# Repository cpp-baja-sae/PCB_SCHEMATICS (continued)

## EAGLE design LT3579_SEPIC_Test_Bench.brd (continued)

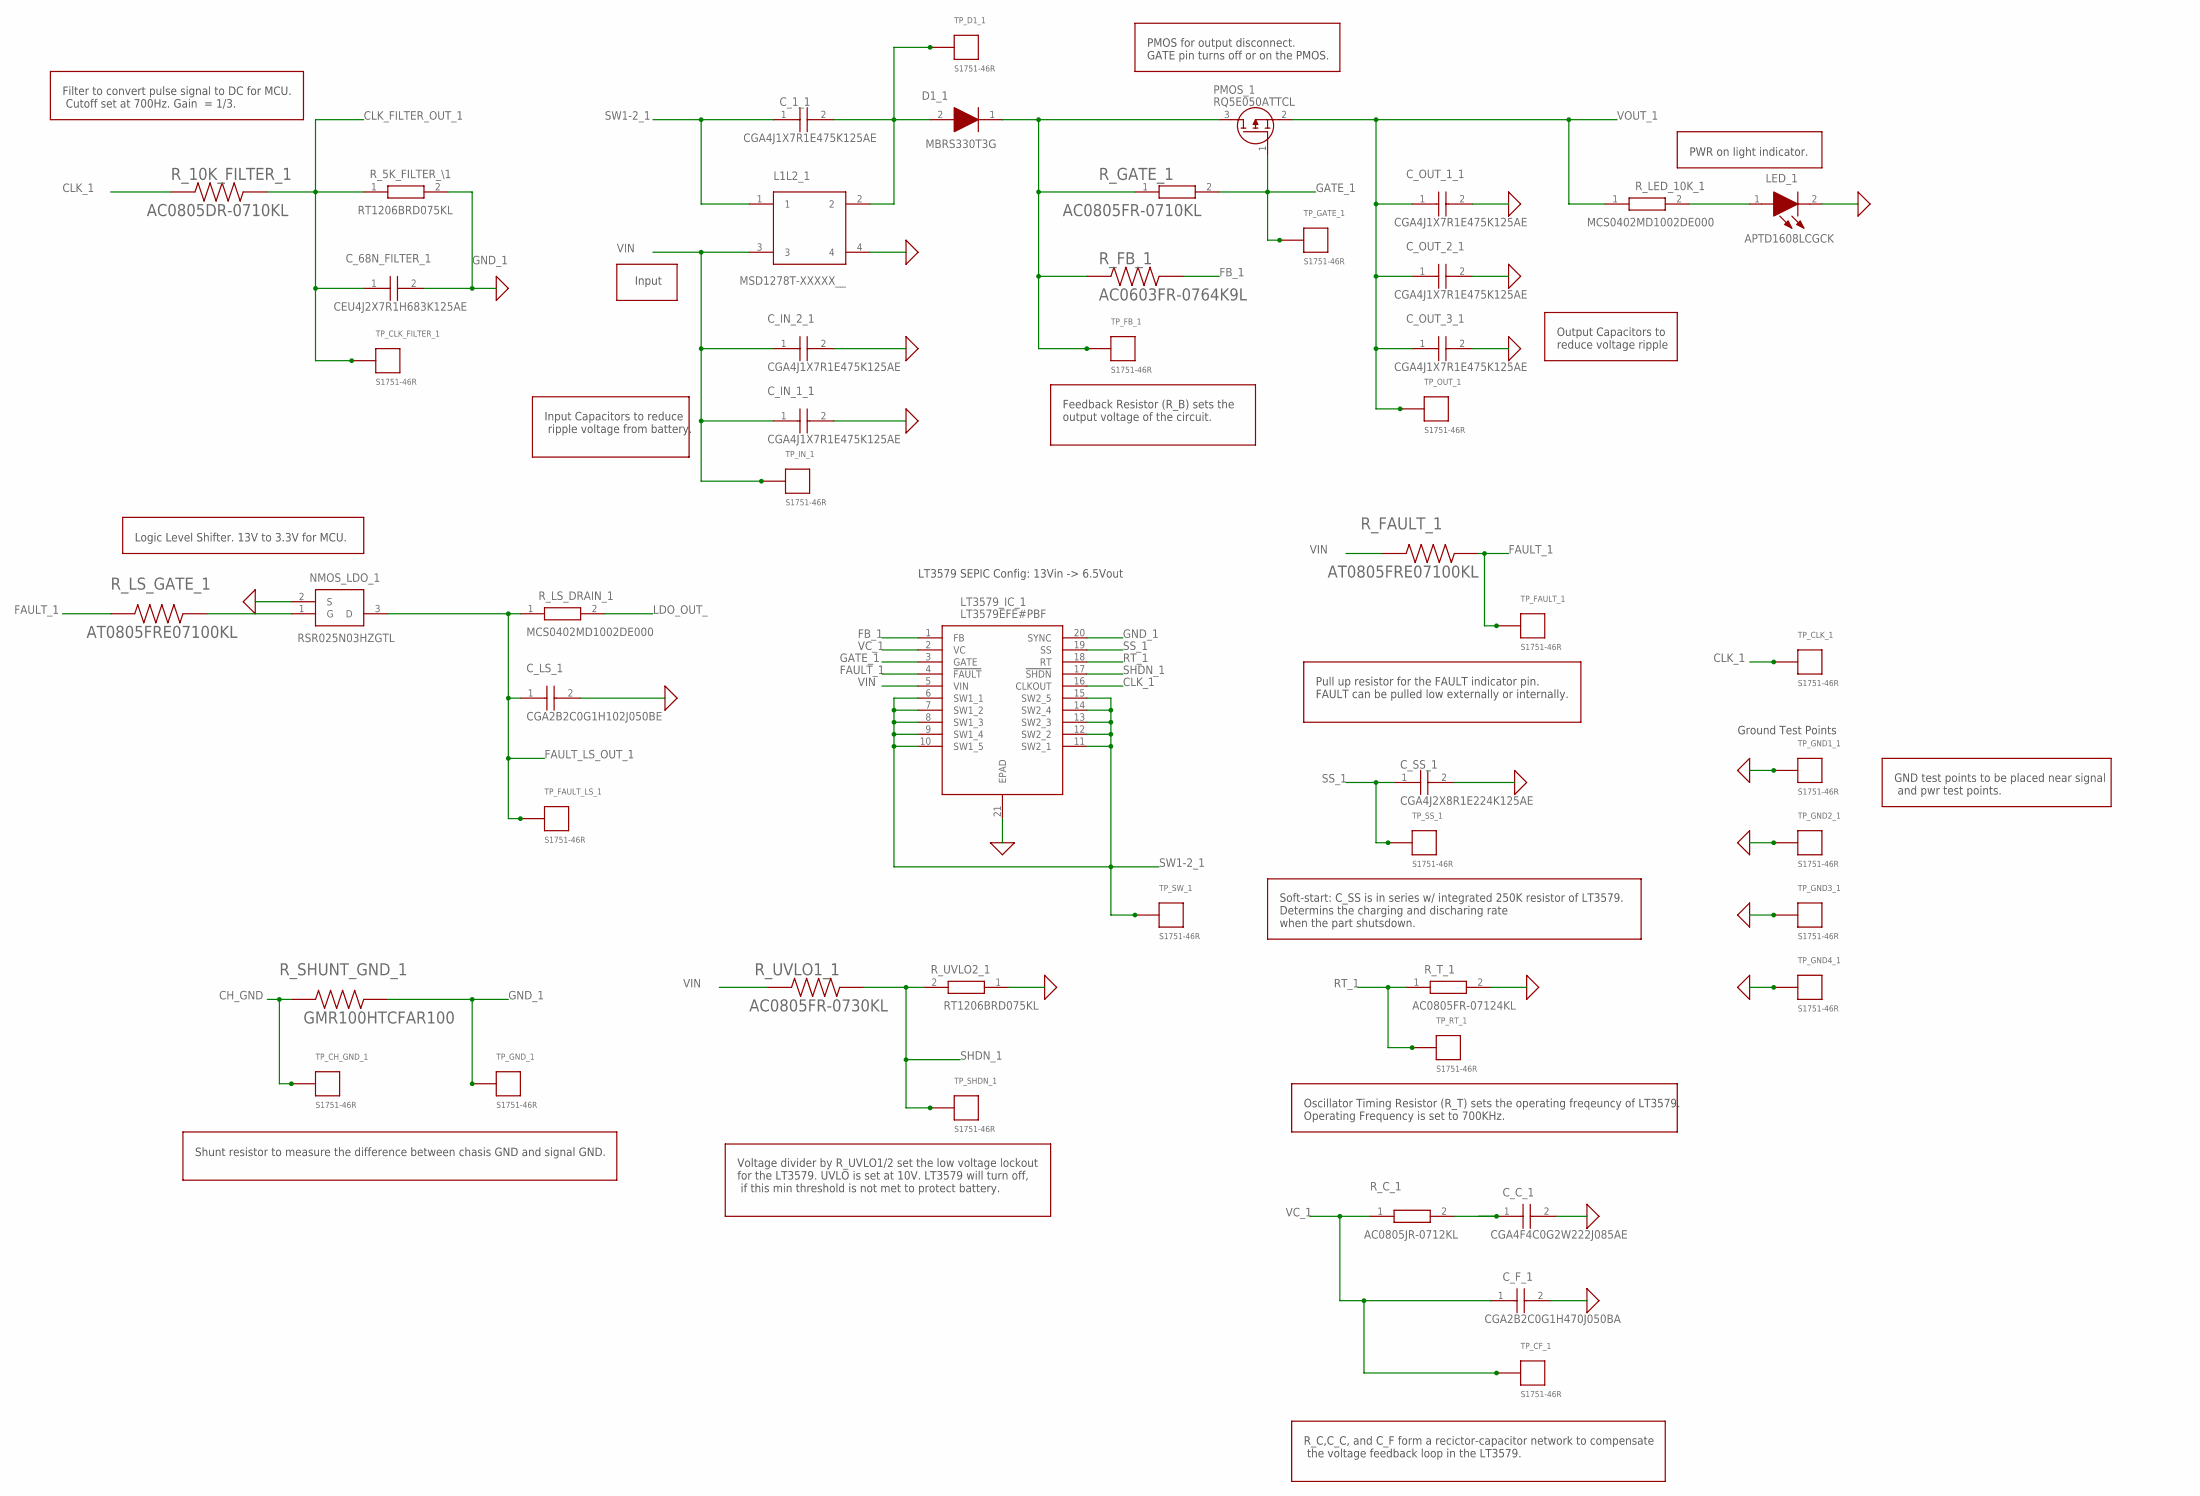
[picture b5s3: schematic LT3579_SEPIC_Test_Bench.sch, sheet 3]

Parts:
C_1_1: CGA4J1X7R1E475K125AE; CAPC2012X145N
C_68N_FILTER_1: CEU4J2X7R1H683K125AE; CAPC2013X150N
C_C_1: CGA4F4C0G2W222J085AE; CAPC2012X100N
C_F_1: CGA2B2C0G1H470J050BA; CAPC1005X55N
C_IN_1_1, C_IN_2_1: CGA4J1X7R1E475K125AE; CAPC2012X145N
C_LS_1: CGA2B2C0G1H102J050BE; CAPC1005X55N
C_OUT_1_1, C_OUT_2_1, C_OUT_3_1: CGA4J1X7R1E475K125AE; CAPC2012X145N
C_SS_1: CGA4J2X8R1E224K125AE; CAPC2012X145N
D1_1: MBRS330T3G; DIOM7958X256N
L1L2_1: MSD1278T-XXXXX__; MSD1278T-822MLXX
LED_1: APTD1608LCGCK; APT1608CGCK
LT3579_IC_1: LT3579EFE#PBF; SOP65P640X120-21N
NMOS_LDO_1: RSR025N03HZGTL; SOT95P280X100-3N
PMOS_1: RQ5E050ATTCL; SOT95P280X100-3N
R_5K_FILTER_\1: RT1206BRD075KL; RESC3116X65N
R_10K_FILTER_1: AC0805DR-0710KL; RESC2012X60N
R_C_1: AC0805JR-0712KL; RESC2012X60N
R_FAULT_1: AT0805FRE07100KL; RESC2012X60N
R_FB_1: AC0603FR-0764K9L; RESC1608X55N
R_GATE_1: AC0805FR-0710KL; RESC2012X60N
R_LED_10K_1: MCS0402MD1002DE000; RESC1005X37N
R_LS_DRAIN_1: MCS0402MD1002DE000; RESC1005X37N
R_LS_GATE_1: AT0805FRE07100KL; RESC2012X60N
R_SHUNT_GND_1: GMR100HTCFAR100; RESC6432X55N
R_T_1: AC0805FR-07124KL; RESC2012X60N
R_UVLO1_1: AC0805FR-0730KL; RESC2012X60N
R_UVLO2_1: RT1206BRD075KL; RESC3116X65N
TP_CF_1: S1751-46R; S1751-46R_
TP_CH_GND_1: S1751-46R; S1751-46R_
TP_CLK_1: S1751-46R; S1751-46R_
TP_CLK_FILTER_1: S1751-46R; S1751-46R_
TP_D1_1: S1751-46R; S1751-46R_
TP_FAULT_1: S1751-46R; S1751-46R_
TP_FAULT_LS_1: S1751-46R; S1751-46R_
TP_FB_1: S1751-46R; S1751-46R_
TP_GATE_1: S1751-46R; S1751-46R_
TP_GND1_1, TP_GND2_1, TP_GND3_1, TP_GND4_1: S1751-46R; S1751-46R_
TP_GND_1: S1751-46R; S1751-46R_
TP_IN_1: S1751-46R; S1751-46R_
TP_OUT_1: S1751-46R; S1751-46R_
TP_RT_1: S1751-46R; S1751-46R_
TP_SHDN_1: S1751-46R; S1751-46R_
TP_SS_1: S1751-46R; S1751-46R_
TP_SW_1: S1751-46R; S1751-46R_

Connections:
CH_GND: R_SHUNT_GND_1.1, TP_CH_GND_1.1; also elsewhere on the board
CLK_1: LT3579_IC_1.16 (CLKOUT), R_10K_FILTER_1.1, TP_CLK_1.1; also elsewhere on the board
FAULT_1: LT3579_IC_1.4 (!FAULT), R_FAULT_1.1, R_LS_GATE_1.1, TP_FAULT_1.1
FAULT_LS_OUT_1: C_LS_1.1, NMOS_LDO_1.3 (D), R_LS_DRAIN_1.1, TP_FAULT_LS_1.1; also elsewhere on the board
FB_1: LT3579_IC_1.1 (FB), R_FB_1.2
GATE_1: LT3579_IC_1.3 (GATE), PMOS_1.1 (G), R_GATE_1.2, TP_GATE_1.1
GND_1: C_68N_FILTER_1.2, C_C_1.2, C_F_1.2, C_IN_1_1.2, C_IN_2_1.2, C_LS_1.2, C_OUT_1_1.2, C_OUT_2_1.2, C_OUT_3_1.2, C_SS_1.2, L1L2_1.4, LED_1.2 (K), LT3579_IC_1.20 (SYNC), LT3579_IC_1.21 (EPAD), NMOS_LDO_1.2 (S), R_5K_FILTER_\1.2, R_SHUNT_GND_1.2, R_T_1.2, R_UVLO2_1.1, TP_GND1_1.1, TP_GND2_1.1, TP_GND3_1.1, TP_GND4_1.1, TP_GND_1.1; also elsewhere on the board
LDO_OUT_: R_LS_DRAIN_1.2; also elsewhere on the board
unnamed: C_1_1.2, D1_1.2 (A), L1L2_1.2, TP_D1_1.1
unnamed: C_C_1.1, R_C_1.2
unnamed: D1_1.1 (K), PMOS_1.3 (D), R_FB_1.1, R_GATE_1.1, TP_FB_1.1
unnamed: NMOS_LDO_1.1 (G), R_LS_GATE_1.2
unnamed: LED_1.1 (A), R_LED_10K_1.2
unnamed: C_68N_FILTER_1.1, R_5K_FILTER_\1.1, R_10K_FILTER_1.2, TP_CLK_FILTER_1.1
RT_1: LT3579_IC_1.18 (RT), R_T_1.1, TP_RT_1.1
SHDN_1: LT3579_IC_1.17 (!SHDN), R_UVLO1_1.1, R_UVLO2_1.2, TP_SHDN_1.1
SS_1: C_SS_1.1, LT3579_IC_1.19 (SS), TP_SS_1.1
SW1-2_1: C_1_1.1, L1L2_1.1, LT3579_IC_1.6 (SW1_1), LT3579_IC_1.7 (SW1_2), LT3579_IC_1.8 (SW1_3), LT3579_IC_1.9 (SW1_4), LT3579_IC_1.10 (SW1_5), LT3579_IC_1.11 (SW2_1), LT3579_IC_1.12 (SW2_2), LT3579_IC_1.13 (SW2_3), LT3579_IC_1.14 (SW2_4), LT3579_IC_1.15 (SW2_5), TP_SW_1.1
VC_1: C_F_1.1, LT3579_IC_1.2 (VC), R_C_1.1, TP_CF_1.1
VIN: C_IN_1_1.1, C_IN_2_1.1, L1L2_1.3, LT3579_IC_1.5 (VIN), R_FAULT_1.2, R_UVLO1_1.2, TP_IN_1.1; also elsewhere on the board
VOUT_1: C_OUT_1_1.1, C_OUT_2_1.1, C_OUT_3_1.1, PMOS_1.2 (S), R_LED_10K_1.1, TP_OUT_1.1; also elsewhere on the board

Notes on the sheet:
LT3579 SEPIC Config: 13Vin -> 6.5Vout
Ground Test Points
Filter to convert pulse signal to DC for MCU. Cutoff set at 700Hz. Gain = 1/3.
Logic Level Shifter. 13V to 3.3V for MCU.
Voltage divider by R_UVLO1/2 set the low voltage lockout for the LT3579. UVLO is set at 10V. LT3579 will turn off, if this min threshold is not met to protect battery.
R_C,C_C, and C_F form a recictor-capacitor network to compensate the voltage feedback loop in the LT3579.
Oscillator Timing Resistor (R_T) sets the operating freqeuncy of LT3579. Operating Frequency is set to 700KHz.
Soft-start: C_SS is in series w/ integrated 250K resistor of LT3579. Determins the charging and discharing rate when the part shutsdown.
GND test points to be placed near signal and pwr test points.
Pull up resistor for the FAULT indicator pin. FAULT can be pulled low externally or internally.
PWR on light indicator.
Output Capacitors to reduce voltage ripple
Feedback Resistor (R_B) sets the output voltage of the circuit.
PMOS for output disconnect. GATE pin turns off or on the PMOS.
Input Capacitors to reduce ripple voltage from battery.
Input
Shunt resistor to measure the difference between chasis GND and signal GND.

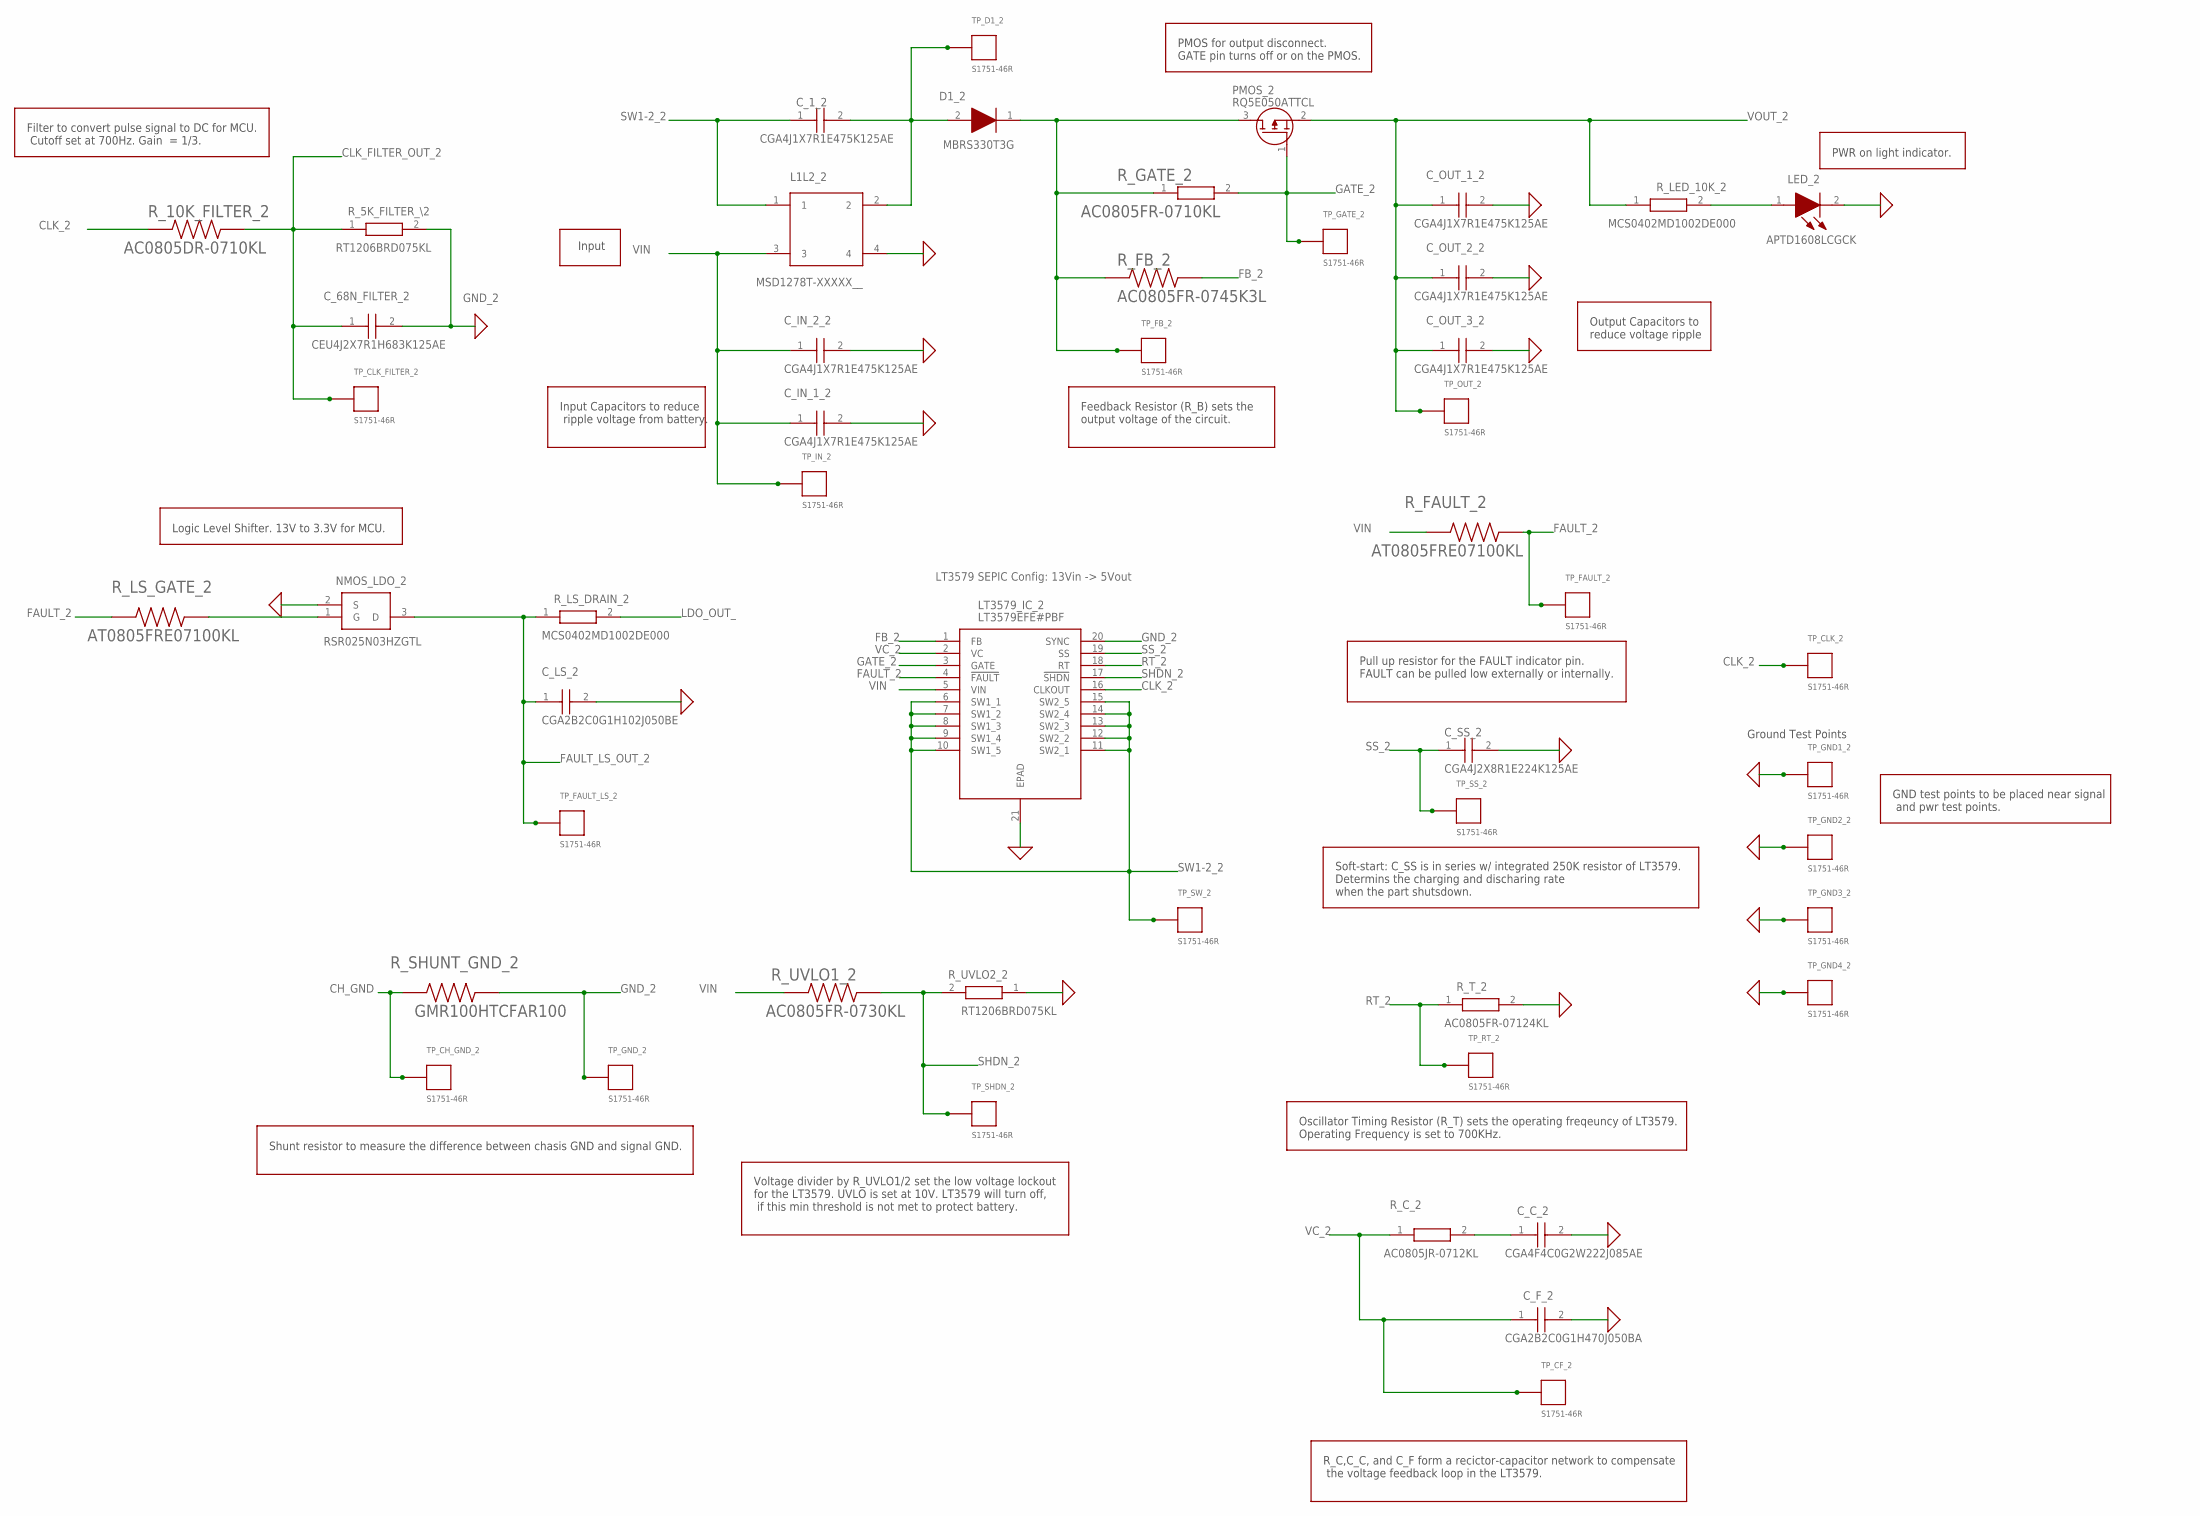
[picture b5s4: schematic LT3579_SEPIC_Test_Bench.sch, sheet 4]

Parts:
C_1_2: CGA4J1X7R1E475K125AE; CAPC2012X145N
C_68N_FILTER_2: CEU4J2X7R1H683K125AE; CAPC2013X150N
C_C_2: CGA4F4C0G2W222J085AE; CAPC2012X100N
C_F_2: CGA2B2C0G1H470J050BA; CAPC1005X55N
C_IN_1_2, C_IN_2_2: CGA4J1X7R1E475K125AE; CAPC2012X145N
C_LS_2: CGA2B2C0G1H102J050BE; CAPC1005X55N
C_OUT_1_2, C_OUT_2_2, C_OUT_3_2: CGA4J1X7R1E475K125AE; CAPC2012X145N
C_SS_2: CGA4J2X8R1E224K125AE; CAPC2012X145N
D1_2: MBRS330T3G; DIOM7958X256N
L1L2_2: MSD1278T-XXXXX__; MSD1278T-822MLXX
LED_2: APTD1608LCGCK; APT1608CGCK
LT3579_IC_2: LT3579EFE#PBF; SOP65P640X120-21N
NMOS_LDO_2: RSR025N03HZGTL; SOT95P280X100-3N
PMOS_2: RQ5E050ATTCL; SOT95P280X100-3N
R_5K_FILTER_\2: RT1206BRD075KL; RESC3116X65N
R_10K_FILTER_2: AC0805DR-0710KL; RESC2012X60N
R_C_2: AC0805JR-0712KL; RESC2012X60N
R_FAULT_2: AT0805FRE07100KL; RESC2012X60N
R_FB_2: AC0805FR-0745K3L; RESC2012X60N
R_GATE_2: AC0805FR-0710KL; RESC2012X60N
R_LED_10K_2: MCS0402MD1002DE000; RESC1005X37N
R_LS_DRAIN_2: MCS0402MD1002DE000; RESC1005X37N
R_LS_GATE_2: AT0805FRE07100KL; RESC2012X60N
R_SHUNT_GND_2: GMR100HTCFAR100; RESC6432X55N
R_T_2: AC0805FR-07124KL; RESC2012X60N
R_UVLO1_2: AC0805FR-0730KL; RESC2012X60N
R_UVLO2_2: RT1206BRD075KL; RESC3116X65N
TP_CF_2: S1751-46R; S1751-46R_
TP_CH_GND_2: S1751-46R; S1751-46R_
TP_CLK_2: S1751-46R; S1751-46R_
TP_CLK_FILTER_2: S1751-46R; S1751-46R_
TP_D1_2: S1751-46R; S1751-46R_
TP_FAULT_2: S1751-46R; S1751-46R_
TP_FAULT_LS_2: S1751-46R; S1751-46R_
TP_FB_2: S1751-46R; S1751-46R_
TP_GATE_2: S1751-46R; S1751-46R_
TP_GND1_2, TP_GND2_2, TP_GND3_2, TP_GND4_2: S1751-46R; S1751-46R_
TP_GND_2: S1751-46R; S1751-46R_
TP_IN_2: S1751-46R; S1751-46R_
TP_OUT_2: S1751-46R; S1751-46R_
TP_RT_2: S1751-46R; S1751-46R_
TP_SHDN_2: S1751-46R; S1751-46R_
TP_SS_2: S1751-46R; S1751-46R_
TP_SW_2: S1751-46R; S1751-46R_

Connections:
CH_GND: R_SHUNT_GND_2.1, TP_CH_GND_2.1; also elsewhere on the board
CLK_2: LT3579_IC_2.16 (CLKOUT), R_10K_FILTER_2.1, TP_CLK_2.1; also elsewhere on the board
FAULT_2: LT3579_IC_2.4 (!FAULT), R_FAULT_2.1, R_LS_GATE_2.1, TP_FAULT_2.1
FAULT_LS_OUT_2: C_LS_2.1, NMOS_LDO_2.3 (D), R_LS_DRAIN_2.1, TP_FAULT_LS_2.1; also elsewhere on the board
FB_2: LT3579_IC_2.1 (FB), R_FB_2.2
GATE_2: LT3579_IC_2.3 (GATE), PMOS_2.1 (G), R_GATE_2.2, TP_GATE_2.1
GND_2: C_68N_FILTER_2.2, C_C_2.2, C_F_2.2, C_IN_1_2.2, C_IN_2_2.2, C_LS_2.2, C_OUT_1_2.2, C_OUT_2_2.2, C_OUT_3_2.2, C_SS_2.2, L1L2_2.4, LED_2.2 (K), LT3579_IC_2.20 (SYNC), LT3579_IC_2.21 (EPAD), NMOS_LDO_2.2 (S), R_5K_FILTER_\2.2, R_SHUNT_GND_2.2, R_T_2.2, R_UVLO2_2.1, TP_GND1_2.1, TP_GND2_2.1, TP_GND3_2.1, TP_GND4_2.1, TP_GND_2.1; also elsewhere on the board
LDO_OUT_: R_LS_DRAIN_2.2; also elsewhere on the board
unnamed: C_1_2.2, D1_2.2 (A), L1L2_2.2, TP_D1_2.1
unnamed: C_C_2.1, R_C_2.2
unnamed: D1_2.1 (K), PMOS_2.3 (D), R_FB_2.1, R_GATE_2.1, TP_FB_2.1
unnamed: NMOS_LDO_2.1 (G), R_LS_GATE_2.2
unnamed: LED_2.1 (A), R_LED_10K_2.2
unnamed: C_68N_FILTER_2.1, R_5K_FILTER_\2.1, R_10K_FILTER_2.2, TP_CLK_FILTER_2.1
RT_2: LT3579_IC_2.18 (RT), R_T_2.1, TP_RT_2.1
SHDN_2: LT3579_IC_2.17 (!SHDN), R_UVLO1_2.1, R_UVLO2_2.2, TP_SHDN_2.1
SS_2: C_SS_2.1, LT3579_IC_2.19 (SS), TP_SS_2.1
SW1-2_2: C_1_2.1, L1L2_2.1, LT3579_IC_2.6 (SW1_1), LT3579_IC_2.7 (SW1_2), LT3579_IC_2.8 (SW1_3), LT3579_IC_2.9 (SW1_4), LT3579_IC_2.10 (SW1_5), LT3579_IC_2.11 (SW2_1), LT3579_IC_2.12 (SW2_2), LT3579_IC_2.13 (SW2_3), LT3579_IC_2.14 (SW2_4), LT3579_IC_2.15 (SW2_5), TP_SW_2.1
VC_2: C_F_2.1, LT3579_IC_2.2 (VC), R_C_2.1, TP_CF_2.1
VIN: C_IN_1_2.1, C_IN_2_2.1, L1L2_2.3, LT3579_IC_2.5 (VIN), R_FAULT_2.2, R_UVLO1_2.2, TP_IN_2.1; also elsewhere on the board
VOUT_2: C_OUT_1_2.1, C_OUT_2_2.1, C_OUT_3_2.1, PMOS_2.2 (S), R_LED_10K_2.1, TP_OUT_2.1; also elsewhere on the board

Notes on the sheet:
LT3579 SEPIC Config: 13Vin -> 5Vout
Ground Test Points
Filter to convert pulse signal to DC for MCU. Cutoff set at 700Hz. Gain = 1/3.
Logic Level Shifter. 13V to 3.3V for MCU.
Voltage divider by R_UVLO1/2 set the low voltage lockout for the LT3579. UVLO is set at 10V. LT3579 will turn off, if this min threshold is not met to protect battery.
R_C,C_C, and C_F form a recictor-capacitor network to compensate the voltage feedback loop in the LT3579.
Oscillator Timing Resistor (R_T) sets the operating freqeuncy of LT3579. Operating Frequency is set to 700KHz.
Soft-start: C_SS is in series w/ integrated 250K resistor of LT3579. Determins the charging and discharing rate when the part shutsdown.
GND test points to be placed near signal and pwr test points.
Pull up resistor for the FAULT indicator pin. FAULT can be pulled low externally or internally.
PWR on light indicator.
Output Capacitors to reduce voltage ripple
Feedback Resistor (R_B) sets the output voltage of the circuit.
PMOS for output disconnect. GATE pin turns off or on the PMOS.
Input Capacitors to reduce ripple voltage from battery.
Input
Shunt resistor to measure the difference between chasis GND and signal GND.

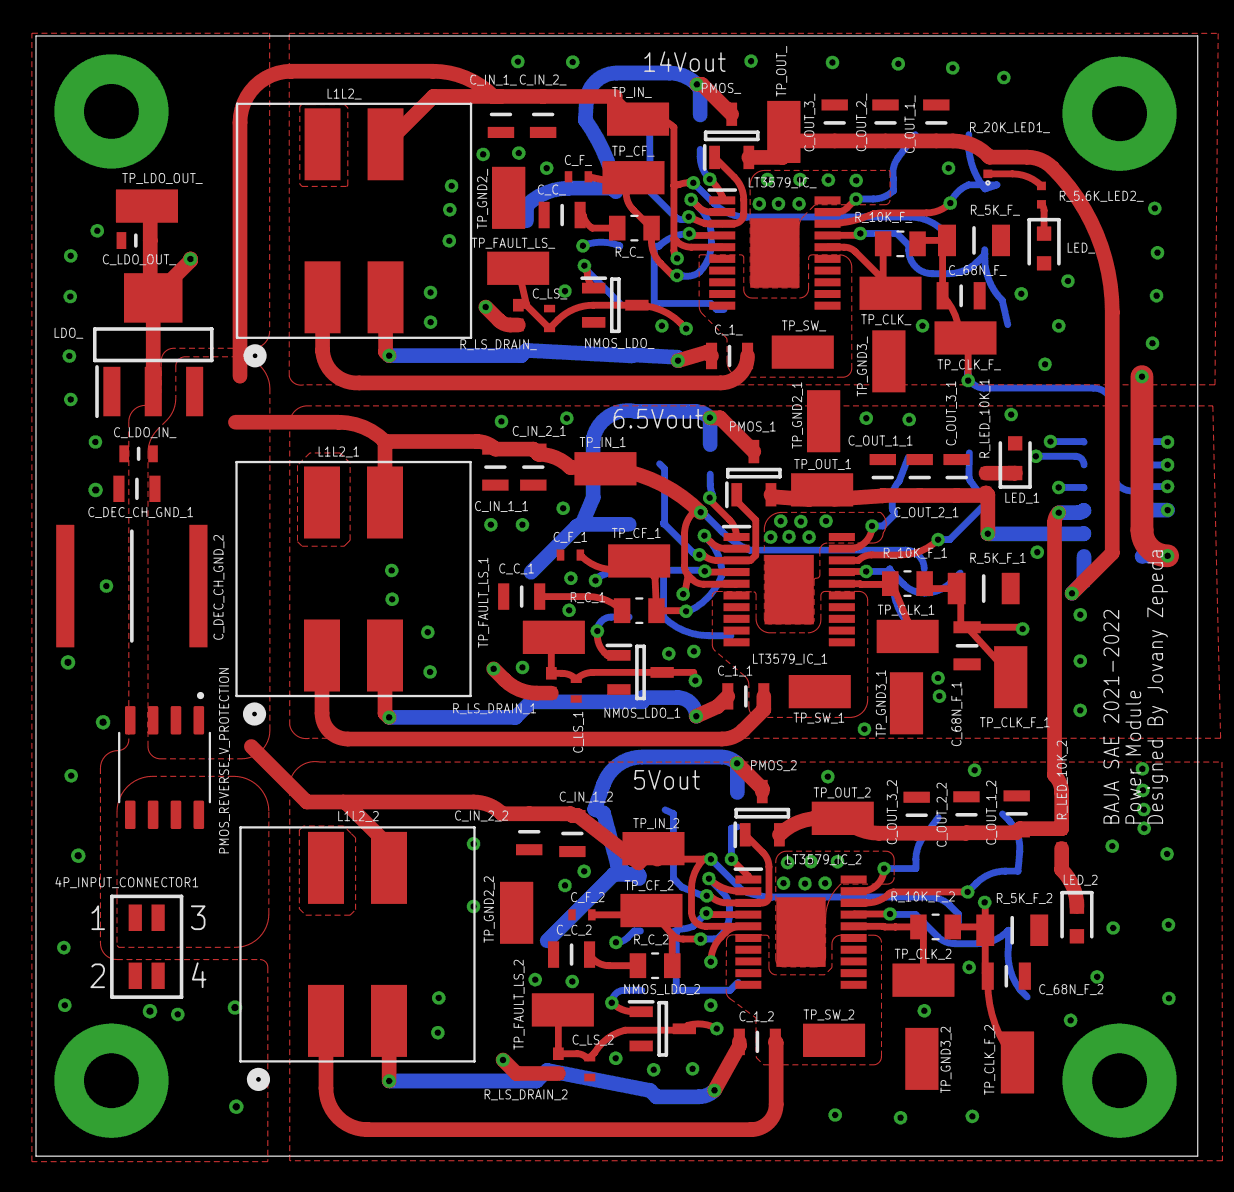
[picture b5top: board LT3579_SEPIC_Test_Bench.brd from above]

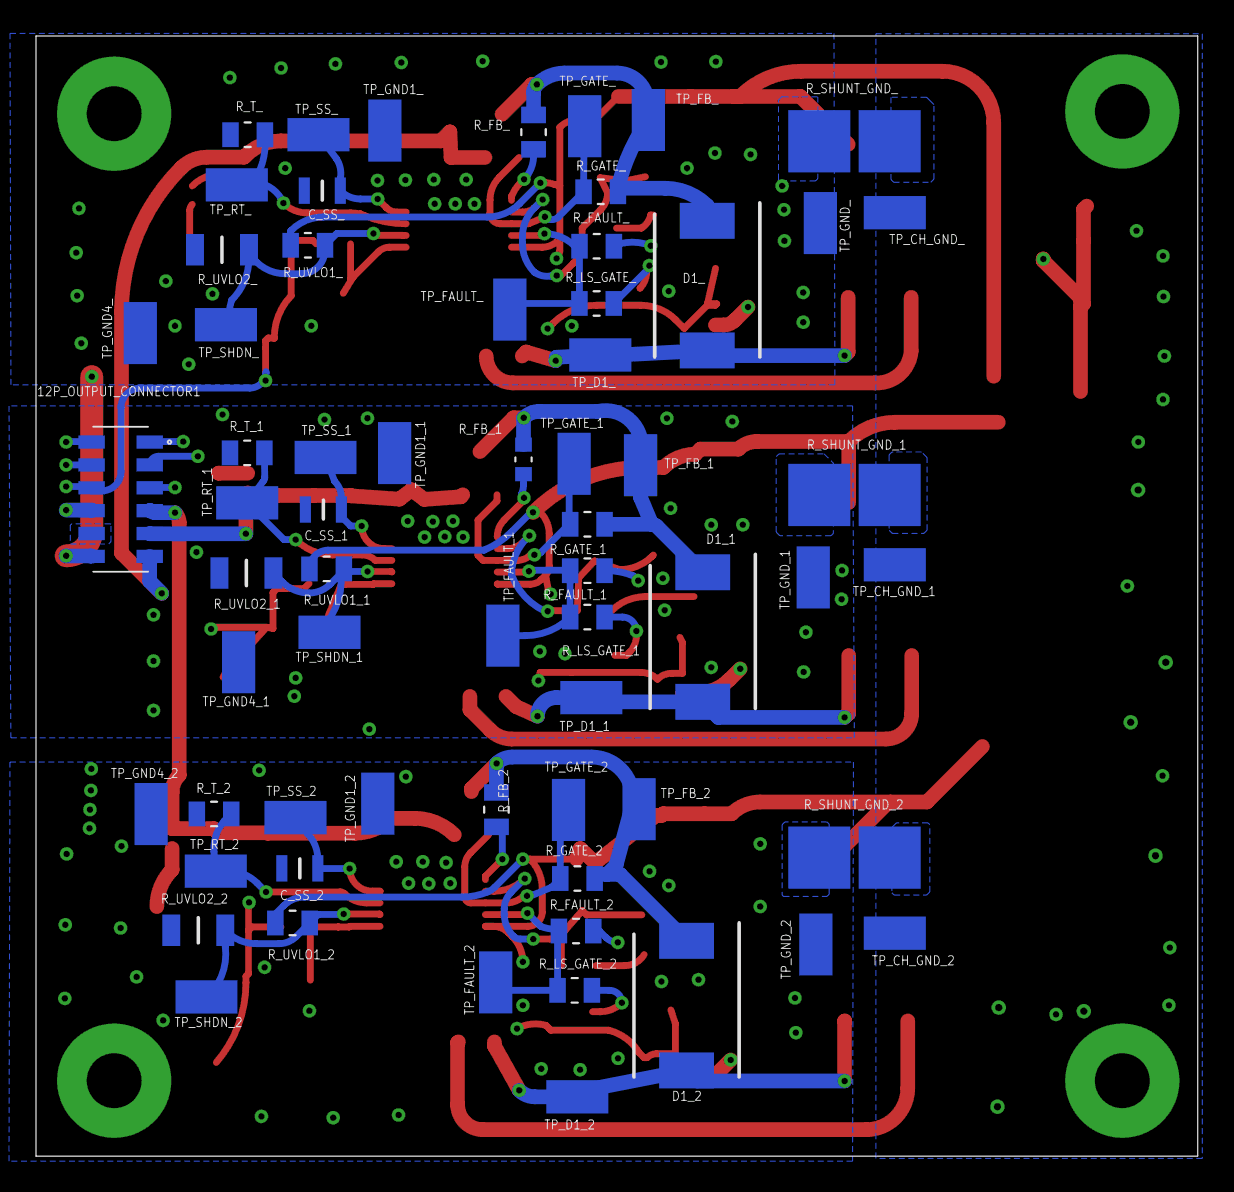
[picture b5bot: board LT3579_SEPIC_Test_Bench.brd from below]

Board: 4 copper layers, 64.5 x 62.2 mm, 164 parts (64 on the bottom side), 59 nets.

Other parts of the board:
C_68N_F_, C_68N_F_1, C_68N_F_2: CEU4J2X7R1H683K125AE; CAPC2013X150N
R_5K_F_, R_5K_F_1, R_5K_F_2: RT1206BRD075KL; RESC3116X65N
R_10K_F_, R_10K_F_1, R_10K_F_2: AC0805DR-0710KL; RESC2012X60N
TP_CLK_F_, TP_CLK_F_1, TP_CLK_F_2: S1751-46R; S1751-46R_

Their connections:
CLK_: R_10K_F_.1; also elsewhere on the board
CLK_1: R_10K_F_1.1; also elsewhere on the board
CLK_2: R_10K_F_2.1; also elsewhere on the board
CLK_FILTER_OUT_: C_68N_F_.1, R_5K_F_.1, R_10K_F_.2, TP_CLK_F_.1; also elsewhere on the board
CLK_FILTER_OUT_1: C_68N_F_1.1, R_5K_F_1.1, R_10K_F_1.2, TP_CLK_F_1.1; also elsewhere on the board
CLK_FILTER_OUT_2: C_68N_F_2.1, R_5K_F_2.1, R_10K_F_2.2, TP_CLK_F_2.1; also elsewhere on the board
GND_: C_68N_F_.2, R_5K_F_.2; also elsewhere on the board
GND_1: C_68N_F_1.2, R_5K_F_1.2; also elsewhere on the board
GND_2: C_68N_F_2.2, R_5K_F_2.2; also elsewhere on the board

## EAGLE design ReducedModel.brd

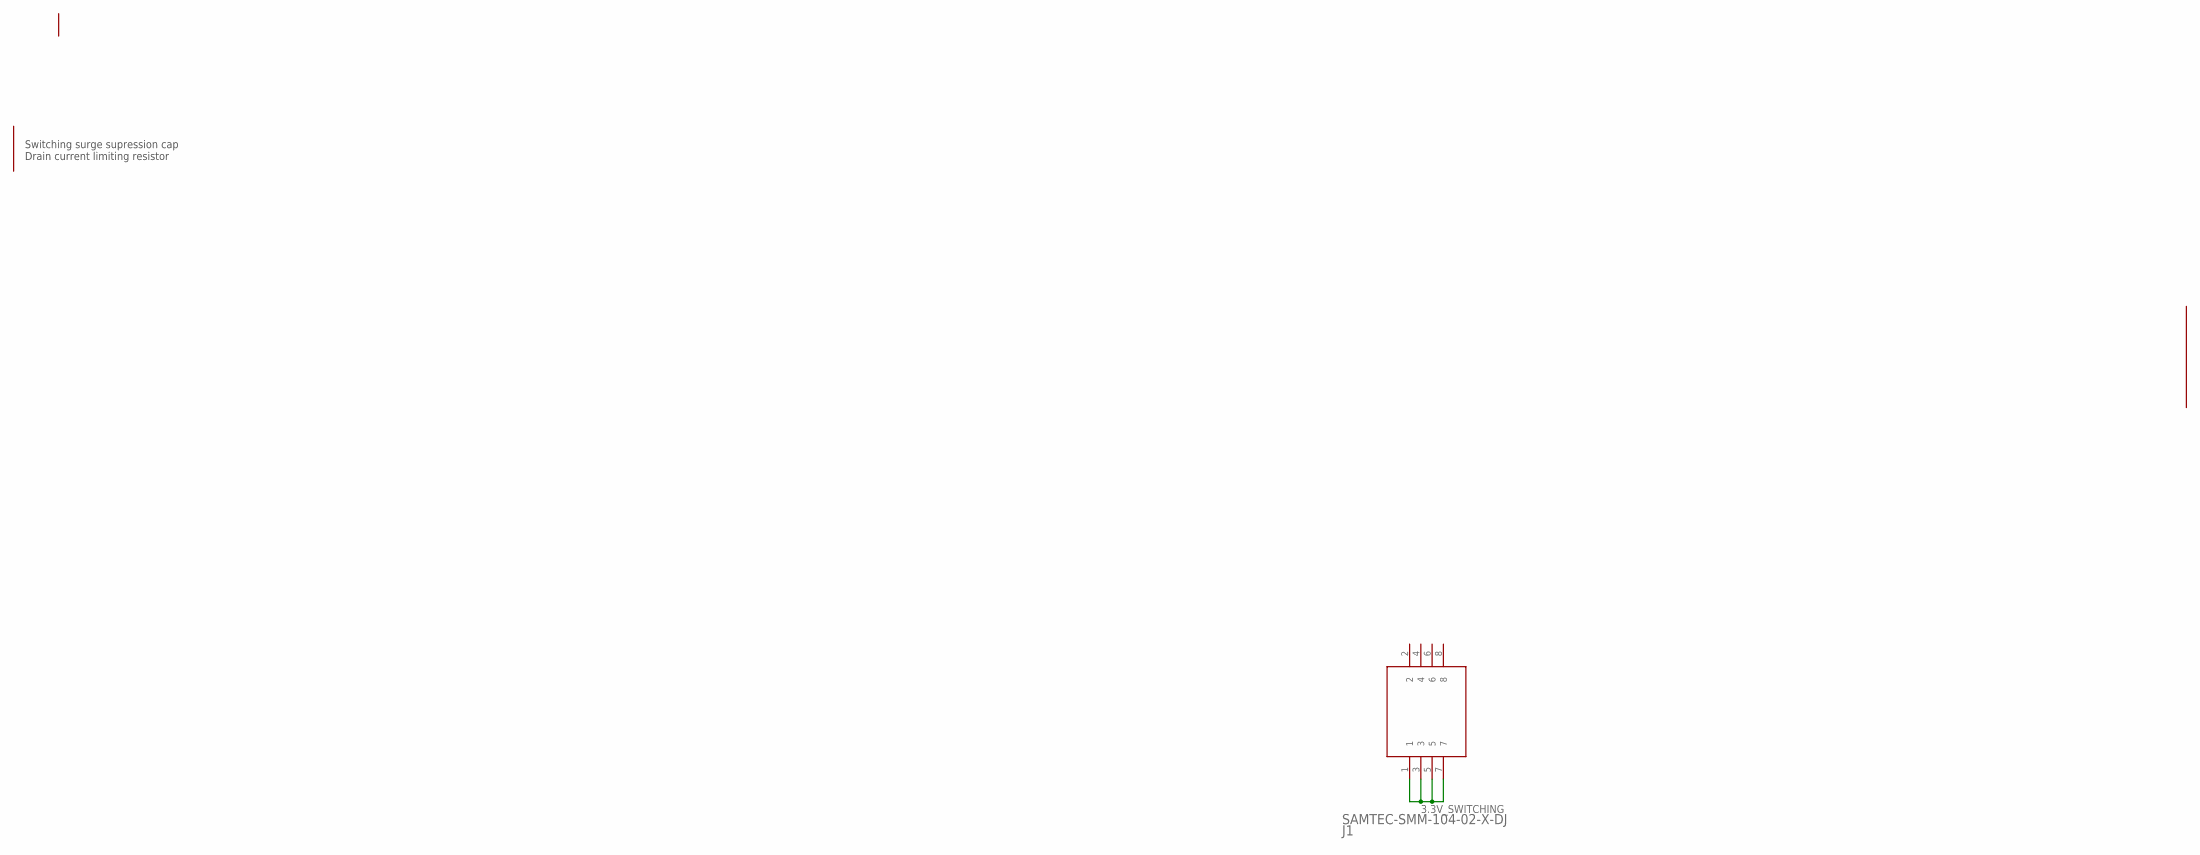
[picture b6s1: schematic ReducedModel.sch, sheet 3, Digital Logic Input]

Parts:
J1: SAMTEC-SMM-104-02-X-DJ; SAMTEC-SMM-104-02-X-D

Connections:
3.3V_SWITCHING: J1.1, J1.3, J1.5, J1.7; also elsewhere on the board

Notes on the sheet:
Switching surge supression cap Drain current limiting resistor

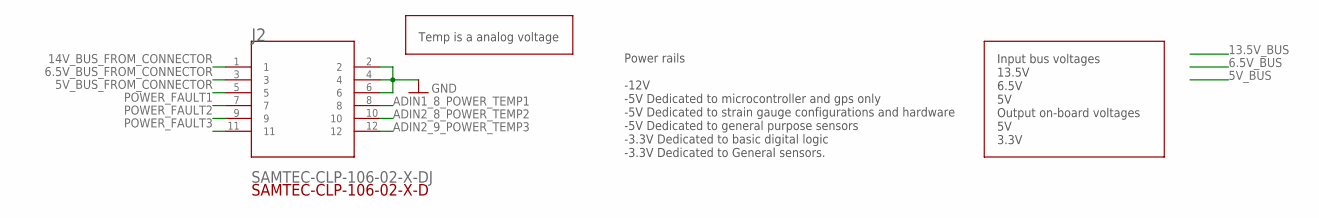
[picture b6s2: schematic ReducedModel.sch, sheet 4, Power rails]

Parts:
J2: SAMTEC-CLP-106-02-X-DJ; SAMTEC-CLP-106-02-X-D

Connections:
5V_BUS_FROM_CONNECTOR: J2.5
6.5V_BUS_FROM_CONNECTOR: J2.3
14V_BUS_FROM_CONNECTOR: J2.1
ADIN1_8_POWER_TEMP1: J2.8
ADIN2_8_POWER_TEMP2: J2.10
ADIN2_9_POWER_TEMP3: J2.12
GND: J2.2, J2.4, J2.6; also elsewhere on the board
POWER_FAULT1: J2.7; also elsewhere on the board
POWER_FAULT2: J2.9; also elsewhere on the board
POWER_FAULT3: J2.11; also elsewhere on the board

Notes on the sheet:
Power rails -12V -5V Dedicated to microcontroller and gps only -5V Dedicated to strain gauge configurations and hardware -5V Dedicated to general purpose sensors -3.3V Dedicated to basic digital logic -3.3V Dedicated to General sensors.
Input bus voltages 13.5V 6.5V 5V Output on-board voltages 5V 3.3V
Temp is a analog voltage

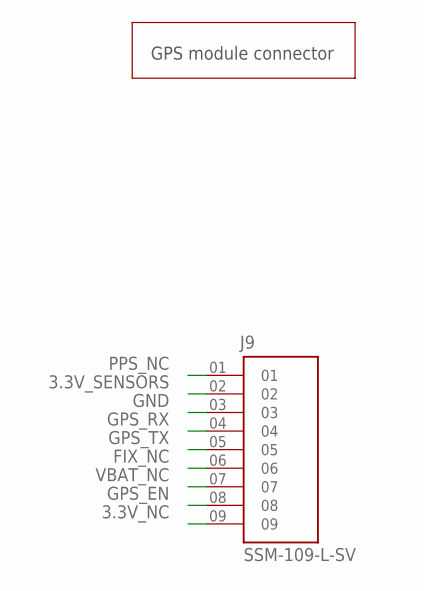
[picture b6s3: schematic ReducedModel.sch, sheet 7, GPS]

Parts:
J9: SSM-109-L-SV; SAMTEC_SSM-109-L-SV

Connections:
3.3V_NC: J9.09
3.3V_SENSORS: J9.02
FIX_NC: J9.06
GND: J9.03; also elsewhere on the board
GPS_EN: J9.08; also elsewhere on the board
GPS_RX: J9.04; also elsewhere on the board
GPS_TX: J9.05; also elsewhere on the board
PPS_NC: J9.01
VBAT_NC: J9.07

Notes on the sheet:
GPS module connector
